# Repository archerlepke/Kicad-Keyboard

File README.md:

# Custom 60% Keyboard From Scratch

A custom mechanical keyboard designed from scratch in KiCad — schematic, PCB, and supporting files.

The goal of this repo is to document and archive my completed work on this project.

## Current Status

> **Manufacturing & Physical Assembly** — The PCB design is complete and the board has been sent to manufacturing.

Future Plans:
- soldering components & microcontroller from digikey(already bought and delivered)
- 3D Print keyboard case
- install switches & keycaps (already bought and on hand)
- install firmware (QMK)

## Renders & PCB Design

The case for the keyboard has been designed and needs to be 3D printed.

**SolidWorks renders of completed case & PCB:**

**KiCad renders:**

**KiCad PCB editor view & schematic:**

## About the Build

The goal of this build was to expand my electronics knowledge while physically creating a project I'd be proud of. This keyboard was designed following the excellent guide by Masterzen, [**Designing a keyboard from scratch**](https://www.masterzen.fr/2020/05/03/designing-a-keyboard-part-1/).

## Repository Structure

```
Keyboard/      KiCad project — open Keyboard/Keyboard.kicad_pro
libraries/     All footprint & symbol libraries (bundled, project-relative paths)
production/    Gerbers, drill files, and BOM as sent to manufacturing
cad/           STEP export and SolidWorks files for the case
images/        Renders and screenshots
```

## Opening the Project

```
git clone https://github.com/archerlepke/Kicad-Keyboard.git
```

Open `Keyboard/Keyboard.kicad_pro` in KiCad (v7 or newer). All custom libraries are
included in the repo and referenced with project-relative paths, so no library
setup is required.

## Library Credits

- [MX_Alps_Hybrid](https://github.com/ai03-2725/MX_Alps_Hybrid) — switch footprints & symbols by ai03
- [Type-C](https://github.com/ai03-2725/Type-C.pretty) — USB-C footprints & symbols by ai03
- [random-keyboard-parts](https://github.com/ai03-2725/random-keyboard-parts.pretty) — misc keyboard parts by ai03

## Tools Used

- **KiCad** — schematic capture and PCB design
- **SolidWorks** — 3D modeling
- **SolidWorks Visualize** — renders
- **QMK** — keyboard firmware (planned)

---

*This is an ongoing project*

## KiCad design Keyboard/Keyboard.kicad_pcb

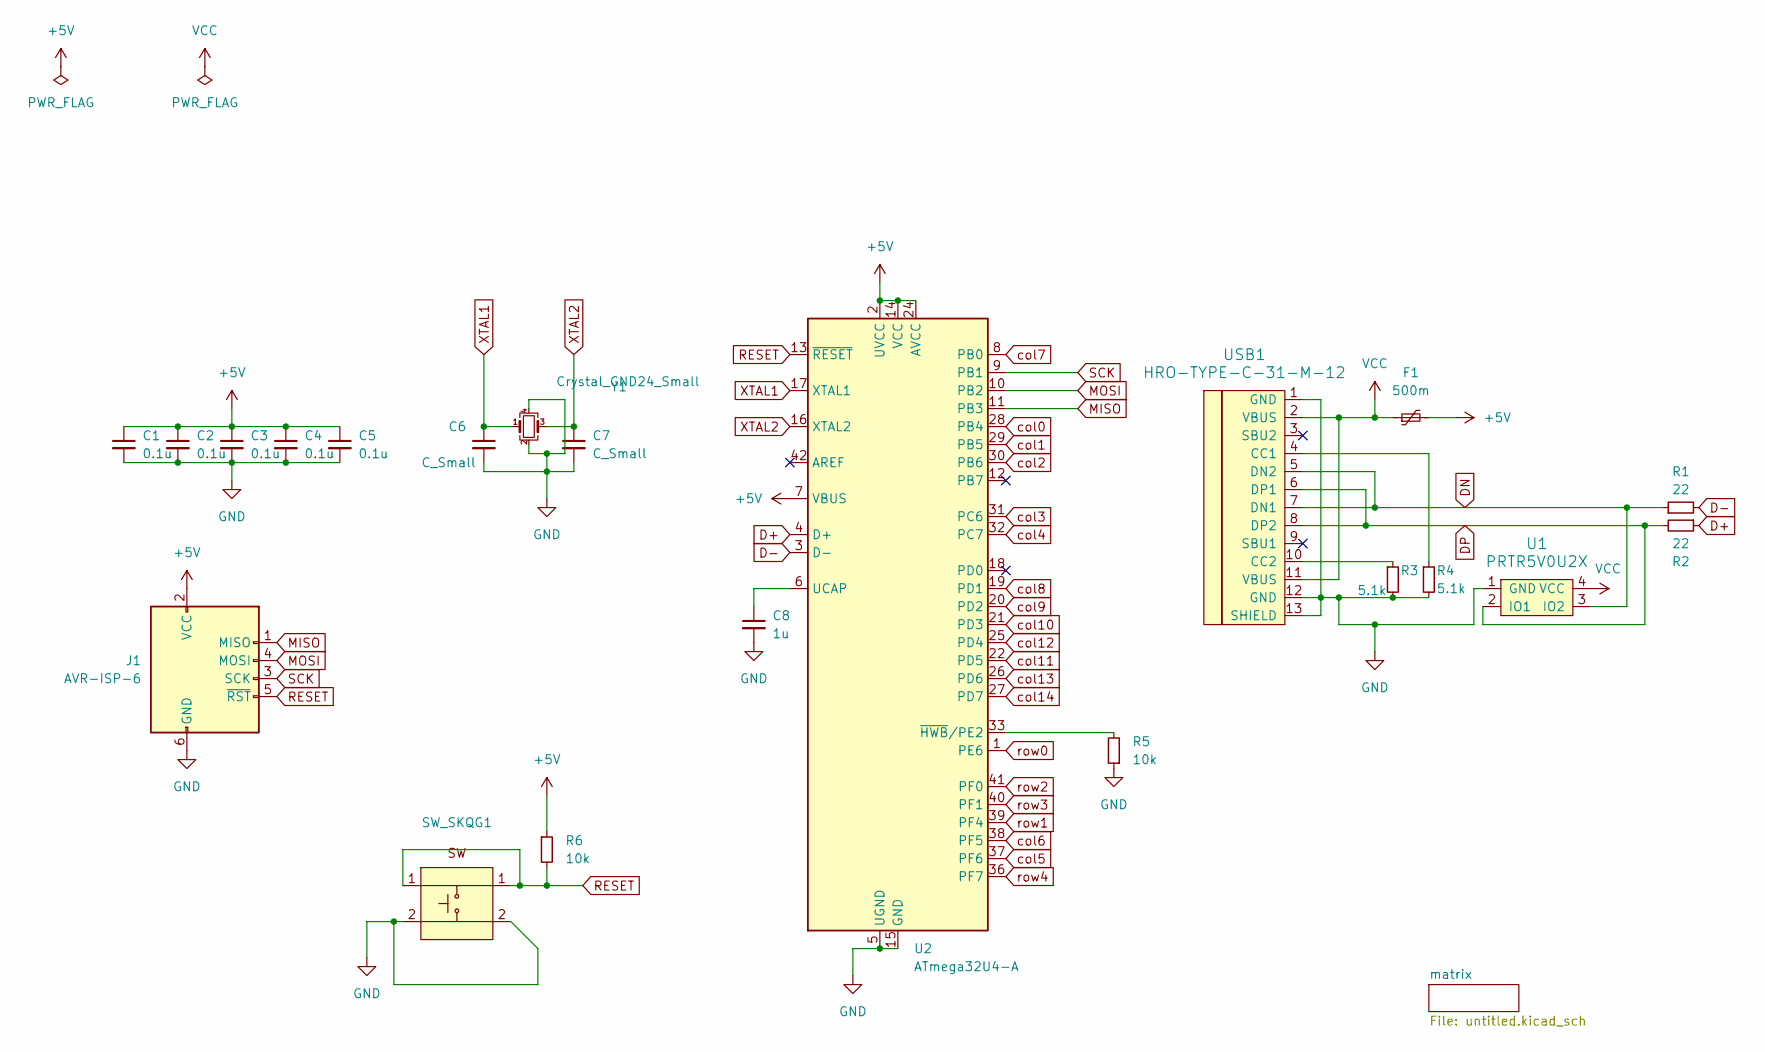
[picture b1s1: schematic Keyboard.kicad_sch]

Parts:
C1, C2, C3, C4, C5: 0.1u; C_0805_2012Metric_Pad1.15x1.40mm_HandSolder
C6, C7: C_Small; C_0805_2012Metric_Pad1.15x1.40mm_HandSolder
C8: 1u; C_0805_2012Metric_Pad1.15x1.40mm_HandSolder
F1: 500m; Fuse_1206_3216Metric_Pad1.42x1.75mm_HandSolder
J1: AVR-ISP-6; Reset_Pretty-Mask
R1, R2: 22; R_0805_2012Metric_Pad1.15x1.40mm_HandSolder
R3, R4: 5.1k; R_0805_2012Metric_Pad1.15x1.40mm_HandSolder
R5, R6: 10k; R_0805_2012Metric_Pad1.15x1.40mm_HandSolder
SW_SKQG1: SW_SPST_SKQG_WithStem
U1: PRTR5V0U2X; SOT143B
U2: ATmega32U4-A; TQFP-44_10x10mm_P0.8mm
USB1: HRO-TYPE-C-31-M-12; HRO-TYPE-C-31-M-12-HandSoldering
Y1: Crystal_GND24_Small; Crystal_SMD_3225-4Pin_3.2x2.5mm_HandSoldering

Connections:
+5V: C1.1, C2.1, C3.1, C4.1, C5.1, F1.2, J1.2 (VCC), R6.1, U2.2 (UVCC), U2.7 (VBUS), U2.14 (VCC), U2.24 (AVCC), U2.34 (VCC), U2.44 (AVCC)
D+: R2.1, U2.4 (D+)
D-: R1.2, U2.3 (D-)
DN: R1.1, U1.3 (IO2), USB1.5 (DN2), USB1.7 (DN1)
DP: R2.2, U1.2 (IO1), USB1.6 (DP1), USB1.8 (DP2)
GND: C1.2, C2.2, C3.2, C4.2, C5.2, C6.2, C7.2, C8.2, J1.6 (GND), R3.2, R4.2, R5.1, SW_SKQG1.2, U1.1 (GND), U2.5 (UGND), U2.15 (GND), U2.23 (GND), U2.35 (GND), U2.43 (GND), USB1.1 (GND), USB1.12 (GND), USB1.13 (SHIELD), Y1.2, Y1.4
MISO: J1.1 (MISO), U2.11 (PB3)
MOSI: J1.4 (MOSI), U2.10 (PB2)
unnamed: C8.1, U2.6 (UCAP)
unnamed: R5.2, U2.33 (~HWB/PE2)
unnamed: R4.1, USB1.4 (CC1)
unnamed: R3.1, USB1.10 (CC2)
RESET: J1.5 (~RST), R6.2, SW_SKQG1.1, U2.13 (~RESET)
SCK: J1.3 (SCK), U2.9 (PB1)
VCC: F1.1, U1.4 (VCC), USB1.2 (VBUS), USB1.11 (VBUS)
XTAL1: C6.1, U2.17 (XTAL1), Y1.1
XTAL2: C7.1, U2.16 (XTAL2), Y1.3
col0: U2.28 (PB4); also elsewhere on the board
col1: U2.29 (PB5); also elsewhere on the board
col2: U2.30 (PB6); also elsewhere on the board
col3: U2.31 (PC6); also elsewhere on the board
col4: U2.32 (PC7); also elsewhere on the board
col5: U2.37 (PF6); also elsewhere on the board
col6: U2.38 (PF5); also elsewhere on the board
col7: U2.8 (PB0); also elsewhere on the board
col8: U2.19 (PD1); also elsewhere on the board
col9: U2.20 (PD2); also elsewhere on the board
col10: U2.21 (PD3); also elsewhere on the board
col11: U2.22 (PD5); also elsewhere on the board
col12: U2.25 (PD4); also elsewhere on the board
col13: U2.26 (PD6); also elsewhere on the board
col14: U2.27 (PD7); also elsewhere on the board
row0: U2.1 (PE6); also elsewhere on the board
row1: U2.39 (PF4); also elsewhere on the board
row2: U2.41 (PF0); also elsewhere on the board
row3: U2.40 (PF1); also elsewhere on the board
row4: U2.36 (PF7); also elsewhere on the board

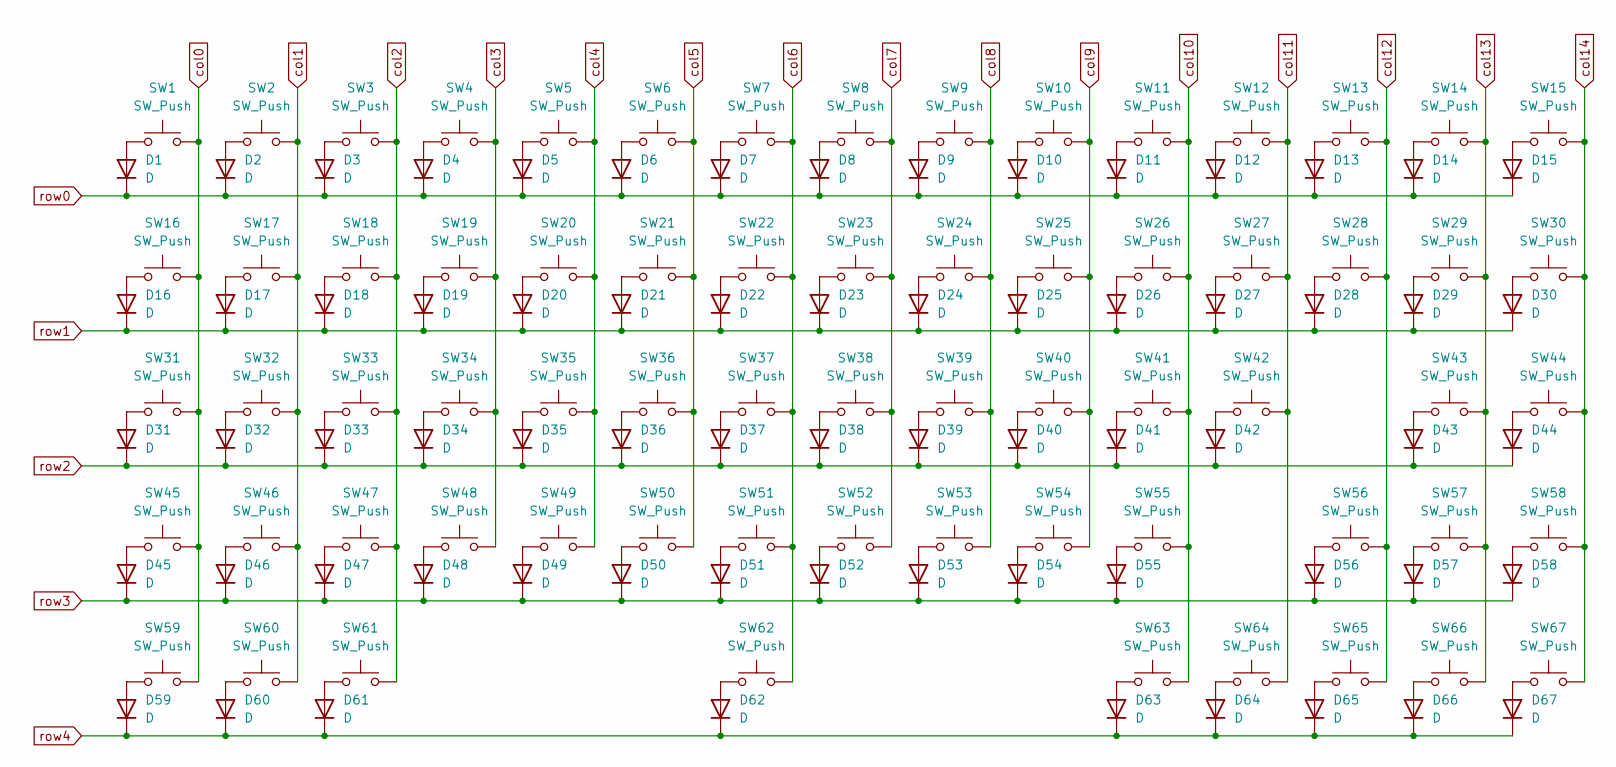
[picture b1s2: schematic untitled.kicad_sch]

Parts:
D1, D2, D3, D4, D5, D6, D7, D8, D9, D10, D11, D12, D13, D14, D15, D16, D17, D18, D19, D20, D21, D22, D23, D24, D25, D26, D27, D28, D29, D30, D31, D32, D33, D34, D35, D36, D37, D38, D39, D40, D41, D42, D43, D44, D45, D46, D47, D48, D49, D50, D51, D52, D53, D54, D55, D56, D57, D58, D59, D60, D61, D62, D63, D64, D65, D66, D67: D; D_SOD-123
SW1, SW2, SW3, SW4, SW5, SW6, SW7, SW8, SW9, SW10, SW11, SW12, SW13, SW15, SW17, SW18, SW19, SW20, SW21, SW22, SW23, SW24, SW25, SW26, SW27, SW28, SW30, SW32, SW33, SW34, SW35, SW36, SW37, SW38, SW39, SW40, SW41, SW42, SW44, SW46, SW47, SW48, SW49, SW50, SW51, SW52, SW53, SW54, SW55, SW57, SW58, SW63, SW65, SW66, SW67: SW_Push; ALPS-1U
SW14: SW_Push; ALPS-2U
SW16, SW29, SW59, SW61: SW_Push; ALPS-1.5U
SW31, SW56: SW_Push; ALPS-1.75U
SW43, SW45: SW_Push; ALPS-2.25U
SW60, SW64: SW_Push; ALPS-1.25U
SW62: SW_Push; ALPS-6.5U

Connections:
unnamed: D1.2 (A), SW1.1
unnamed: D2.2 (A), SW2.1
unnamed: D3.2 (A), SW3.1
unnamed: D4.2 (A), SW4.1
unnamed: D5.2 (A), SW5.1
unnamed: D6.2 (A), SW6.1
unnamed: D7.2 (A), SW7.1
unnamed: D8.2 (A), SW8.1
unnamed: D9.2 (A), SW9.1
unnamed: D10.2 (A), SW10.1
unnamed: D11.2 (A), SW11.1
unnamed: D12.2 (A), SW12.1
unnamed: D13.2 (A), SW13.1
unnamed: D14.2 (A), SW14.1
unnamed: D15.2 (A), SW15.1
unnamed: D16.2 (A), SW16.1
unnamed: D17.2 (A), SW17.1
unnamed: D18.2 (A), SW18.1
unnamed: D19.2 (A), SW19.1
unnamed: D20.2 (A), SW20.1
unnamed: D21.2 (A), SW21.1
unnamed: D22.2 (A), SW22.1
unnamed: D23.2 (A), SW23.1
unnamed: D24.2 (A), SW24.1
unnamed: D25.2 (A), SW25.1
unnamed: D26.2 (A), SW26.1
unnamed: D27.2 (A), SW27.1
unnamed: D28.2 (A), SW28.1
unnamed: D29.2 (A), SW29.1
unnamed: D30.2 (A), SW30.1
unnamed: D31.2 (A), SW31.1
unnamed: D32.2 (A), SW32.1
unnamed: D33.2 (A), SW33.1
unnamed: D34.2 (A), SW34.1
unnamed: D35.2 (A), SW35.1
unnamed: D36.2 (A), SW36.1
unnamed: D37.2 (A), SW37.1
unnamed: D38.2 (A), SW38.1
unnamed: D39.2 (A), SW39.1
unnamed: D40.2 (A), SW40.1
unnamed: D41.2 (A), SW41.1
unnamed: D42.2 (A), SW42.1
unnamed: D43.2 (A), SW43.1
unnamed: D44.2 (A), SW44.1
unnamed: D45.2 (A), SW45.1
unnamed: D46.2 (A), SW46.1
unnamed: D47.2 (A), SW47.1
unnamed: D48.2 (A), SW48.1
unnamed: D49.2 (A), SW49.1
unnamed: D50.2 (A), SW50.1
unnamed: D51.2 (A), SW51.1
unnamed: D52.2 (A), SW52.1
unnamed: D53.2 (A), SW53.1
unnamed: D54.2 (A), SW54.1
unnamed: D55.2 (A), SW55.1
unnamed: D56.2 (A), SW56.1
unnamed: D57.2 (A), SW57.1
unnamed: D58.2 (A), SW58.1
unnamed: D59.2 (A), SW59.1
unnamed: D60.2 (A), SW60.1
unnamed: D61.2 (A), SW61.1
unnamed: D62.2 (A), SW62.1
unnamed: D63.2 (A), SW63.1
unnamed: D64.2 (A), SW64.1
unnamed: D65.2 (A), SW65.1
unnamed: D66.2 (A), SW66.1
unnamed: D67.2 (A), SW67.1
col0: SW1.2, SW16.2, SW31.2, SW45.2, SW59.2; also elsewhere on the board
col1: SW2.2, SW17.2, SW32.2, SW46.2, SW60.2; also elsewhere on the board
col2: SW3.2, SW18.2, SW33.2, SW47.2, SW61.2; also elsewhere on the board
col3: SW4.2, SW19.2, SW34.2, SW48.2; also elsewhere on the board
col4: SW5.2, SW20.2, SW35.2, SW49.2; also elsewhere on the board
col5: SW6.2, SW21.2, SW36.2, SW50.2; also elsewhere on the board
col6: SW7.2, SW22.2, SW37.2, SW51.2, SW62.2; also elsewhere on the board
col7: SW8.2, SW23.2, SW38.2, SW52.2; also elsewhere on the board
col8: SW9.2, SW24.2, SW39.2, SW53.2; also elsewhere on the board
col9: SW10.2, SW25.2, SW40.2, SW54.2; also elsewhere on the board
col10: SW11.2, SW26.2, SW41.2, SW55.2, SW63.2; also elsewhere on the board
col11: SW12.2, SW27.2, SW42.2, SW64.2; also elsewhere on the board
col12: SW13.2, SW28.2, SW56.2, SW65.2; also elsewhere on the board
col13: SW14.2, SW29.2, SW43.2, SW57.2, SW66.2; also elsewhere on the board
col14: SW15.2, SW30.2, SW44.2, SW58.2, SW67.2; also elsewhere on the board
row0: D1.1 (K), D2.1 (K), D3.1 (K), D4.1 (K), D5.1 (K), D6.1 (K), D7.1 (K), D8.1 (K), D9.1 (K), D10.1 (K), D11.1 (K), D12.1 (K), D13.1 (K), D14.1 (K), D15.1 (K); also elsewhere on the board
row1: D16.1 (K), D17.1 (K), D18.1 (K), D19.1 (K), D20.1 (K), D21.1 (K), D22.1 (K), D23.1 (K), D24.1 (K), D25.1 (K), D26.1 (K), D27.1 (K), D28.1 (K), D29.1 (K), D30.1 (K); also elsewhere on the board
row2: D31.1 (K), D32.1 (K), D33.1 (K), D34.1 (K), D35.1 (K), D36.1 (K), D37.1 (K), D38.1 (K), D39.1 (K), D40.1 (K), D41.1 (K), D42.1 (K), D43.1 (K), D44.1 (K); also elsewhere on the board
row3: D45.1 (K), D46.1 (K), D47.1 (K), D48.1 (K), D49.1 (K), D50.1 (K), D51.1 (K), D52.1 (K), D53.1 (K), D54.1 (K), D55.1 (K), D56.1 (K), D57.1 (K), D58.1 (K); also elsewhere on the board
row4: D59.1 (K), D60.1 (K), D61.1 (K), D62.1 (K), D63.1 (K), D64.1 (K), D65.1 (K), D66.1 (K), D67.1 (K); also elsewhere on the board

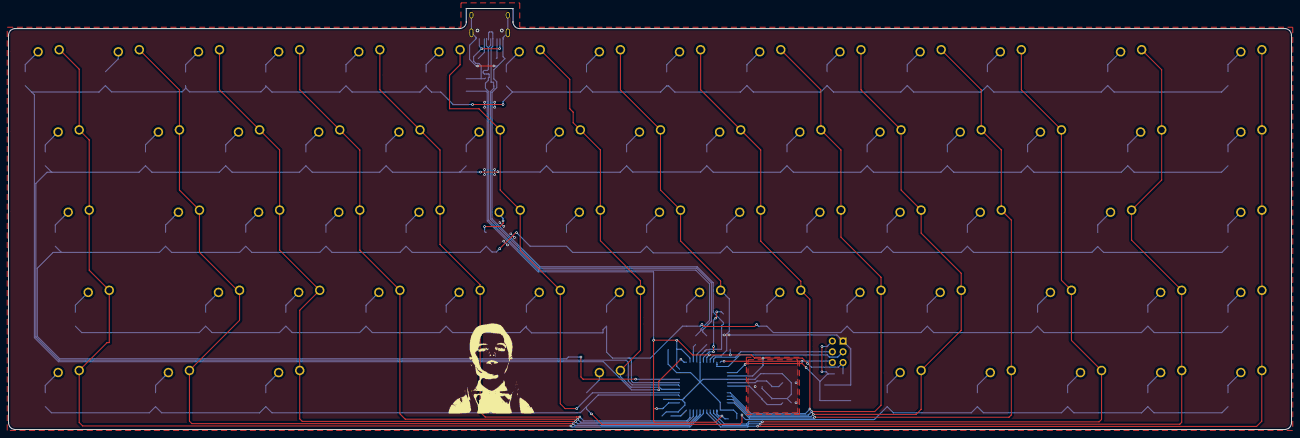
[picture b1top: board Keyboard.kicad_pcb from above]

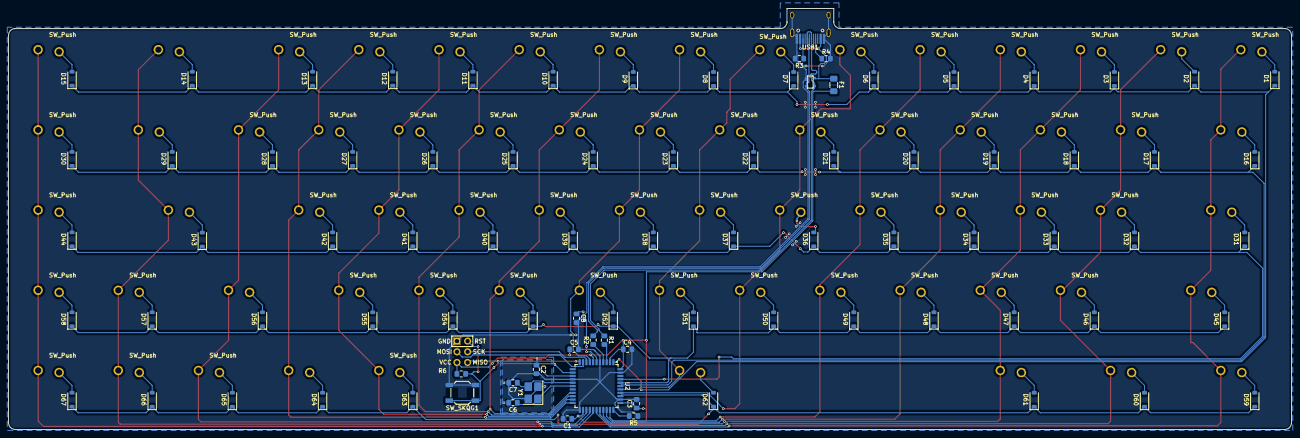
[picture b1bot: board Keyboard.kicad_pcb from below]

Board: 2 copper layers, 304.8 x 100.0 mm, 155 parts (88 on the bottom side), 104 nets.

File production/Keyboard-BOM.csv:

Id,Designator,Footprint,Quantity,Designation,Supplier and ref
1,"C1, C2, C3, C4, C5",C_0805_2012Metric_Pad1.15x1.40mm_HandSolder,5,0.1u,
2,"C6, C7",C_0805_2012Metric_Pad1.15x1.40mm_HandSolder,2,C_Small,
3,C8,C_0805_2012Metric_Pad1.15x1.40mm_HandSolder,1,1u,
4,"D1, D2, D3, D4, D5, D6, D7, D8, D9, D10, D11, D12, D13, D14, D15, D16, D17, D18, D19, D20, D21, D22, D23, D24, D25, D26, D27, D28, D29, D30, D31, D32, D33, D34, D35, D36, D37, D38, D39, D40, D41, D42, D43, D44, D45, D46, D47, D48, D49, D50, D51, D52, D53, D54, D55, D56, D57, D58, D59, D60, D61, D62, D63, D64, D65, D66, D67",D_SOD-123,67,D,
5,F1,Fuse_1206_3216Metric_Pad1.42x1.75mm_HandSolder,1,500m,
6,J1,Reset_Pretty-Mask,1,AVR-ISP-6,
7,"R1, R2",R_0805_2012Metric_Pad1.15x1.40mm_HandSolder,2,22,
8,"R3, R4",R_0805_2012Metric_Pad1.15x1.40mm_HandSolder,2,5.1k,
9,"R5, R6",R_0805_2012Metric_Pad1.15x1.40mm_HandSolder,2,10k,
10,REF**,Untitled,1,Untitled,
11,"SW1, SW2, SW3, SW4, SW5, SW6, SW7, SW8, SW9, SW10, SW11, SW12, SW13, SW15, SW17, SW18, SW19, SW20, SW21, SW22, SW23, SW24, SW25, SW26, SW27, SW28, SW30, SW32, SW33, SW34, SW35, SW36, SW37, SW38, SW39, SW40, SW41, SW42, SW44, SW46, SW47, SW48, SW49, SW50, SW51, SW52, SW53, SW54, SW55, SW57, SW58, SW63, SW65, SW66, SW67",ALPS-1U,55,SW_Push,
12,SW14,ALPS-2U,1,SW_Push,
13,"SW16, SW29, SW59, SW61",ALPS-1.5U,4,SW_Push,
14,"SW31, SW56",ALPS-1.75U,2,SW_Push,
15,"SW43, SW45",ALPS-2.25U,2,SW_Push,
16,"SW60, SW64",ALPS-1.25U,2,SW_Push,
17,SW62,ALPS-6.5U,1,SW_Push,
18,SW_SKQG1,SW_SPST_SKQG_WithStem,1,~,
19,U1,SOT143B,1,PRTR5V0U2X,
20,U2,TQFP-44_10x10mm_P0.8mm,1,ATmega32U4-A,
21,USB1,HRO-TYPE-C-31-M-12-HandSoldering,1,HRO-TYPE-C-31-M-12,
22,Y1,Crystal_SMD_3225-4Pin_3.2x2.5mm_HandSoldering,1,Crystal_GND24_Small,got

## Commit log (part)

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2026-06-17 Initial commit - Adding already completed files
2026-06-17 test
2026-06-17 rename
2026-06-17 file-path-update
2026-06-17 solidworks
2026-06-17 readme
2026-06-17 test1
2026-06-17 images1
2026-06-17 images2
